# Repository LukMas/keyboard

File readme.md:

# icekeys

A short description of the keyboard/project

Keyboard Maintainer: [You](https://github.com/LukMas)  
Hardware Supported: The PCBs, controllers supported  
Hardware Availability: links to where you can find this hardware

Make example for this keyboard (after setting up your build environment):

    make snowflake:default

Note: check here (https://www.pjrc.com/teensy/td_libs_PS2Keyboard.html) if PS/2 mouse works with other pins. 

See [build environment setup](https://docs.qmk.fm/build_environment_setup.html) then the [make instructions](https://docs.qmk.fm/make_instructions.html) for more information.

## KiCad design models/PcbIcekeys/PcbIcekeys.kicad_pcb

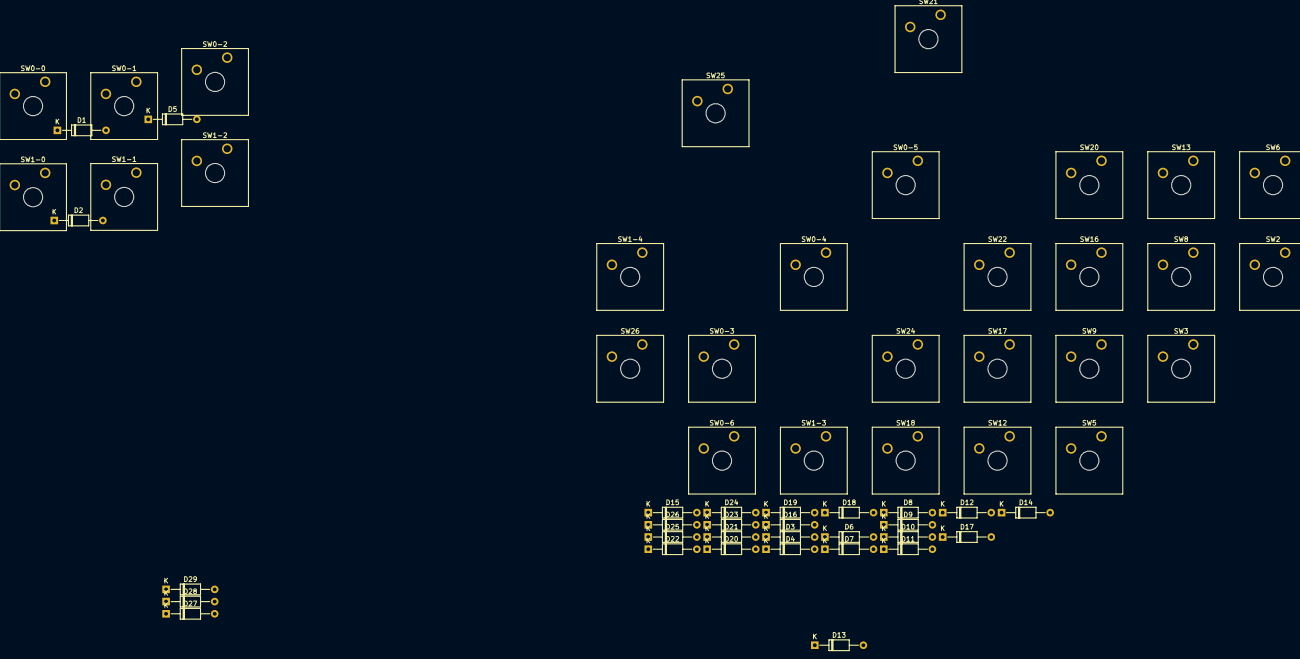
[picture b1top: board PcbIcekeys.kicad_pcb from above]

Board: 2 copper layers, 58 parts (0 on the bottom side), 36 nets, no tracks yet.

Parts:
D1, D2, D3, D4, D5, D6, D7, D8, D9, D10, D11, D12, D13, D14, D15, D16, D17, D18, D19, D20, D21, D22, D23, D24, D25, D26, D27, D28, D29: DIODE; D_DO-35_SOD27_P10.16mm_Horizontal
SW0-0, SW0-1, SW0-2, SW0-3, SW0-4, SW0-5, SW0-6, SW1-0, SW1-1, SW1-2, SW1-3, SW1-4, SW2, SW3, SW5, SW6, SW8, SW9, SW12, SW13, SW16, SW17, SW18, SW20, SW21, SW22, SW24, SW25, SW26: SW_Push; SW_Cherry_MX1A_1.00u_Plate

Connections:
unnamed: D1.1, SW0-0.2
unnamed: D1.2, D5.1, SW0-1.2
unnamed: D2.1, SW1-0.2
unnamed: D2.2, D6.1, SW1-1.2
unnamed: D3.1, SW2.2
unnamed: D3.2, D7.1, SW5.2
unnamed: D4.1, SW3.2
unnamed: D4.2, D8.1, SW6.2
unnamed: D5.2, D9.1, SW0-2.2
unnamed: D6.2, D10.1, SW1-2.2
unnamed: D10.2, D14.1, SW1-3.2
unnamed: D7.2, D11.1, SW8.2
unnamed: D11.2, D15.1, SW12.2
unnamed: D8.2, D12.1, SW9.2
unnamed: D12.2, D16.1, SW13.2
unnamed: D9.2, D13.1, SW0-3.2
unnamed: D13.2, D17.1, SW0-4.2
unnamed: D14.2, D18.1, SW1-4.2
unnamed: D15.2, D19.1, SW16.2
unnamed: D16.2, D20.1, SW17.2
unnamed: D17.2, D22.1, SW0-5.2
unnamed: D18.2, D23.1, SW20.2
unnamed: D19.2, D24.1, SW21.2
unnamed: D20.2, D21.1, SW18.2
unnamed: D21.2, D25.1, SW22.2
unnamed: D22.2, D26.1, SW0-6.2
unnamed: D23.2, D27.1, SW24.2
unnamed: D24.2, D28.1, SW25.2
unnamed: D25.2, D29.1, SW26.2
unnamed: SW0-0.1, SW1-0.1, SW2.1, SW3.1
unnamed: SW0-1.1, SW1-1.1, SW5.1, SW6.1
unnamed: SW0-2.1, SW1-2.1, SW8.1, SW9.1
unnamed: SW0-3.1, SW1-3.1, SW12.1, SW13.1
unnamed: SW0-4.1, SW1-4.1, SW16.1, SW17.1, SW18.1
unnamed: SW0-5.1, SW20.1, SW21.1, SW22.1
unnamed: SW0-6.1, SW24.1, SW25.1, SW26.1

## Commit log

2018-08-09 Initial version of IceKeys keyboard
    Initial version of the keyboad IceKeys.
    In this firt revision only some keys are used. Actually the layout is
    used for understanding how the keys, the macros and the functionalities
    of QMK work.
2018-08-09 Removed files and configured .gitignore
    Temp files have been removed from repository.
    Gitignore has been cofigured to ignore this files in the future.
2018-08-09 Added tne Navi Layer
    The layout now supports a new layer, the Navi Layer, where the mouse
    keys are added.
    It's a LT type, held will activate the layer, tap will activate the tab.
2018-08-10 Mouse Navigation layer - Navi layer
    Added new layer to the keyboard: Navi layer.
    Selectable with holding the tab, it offers the basic mouse movements and
    keys.
2018-09-17 PS/2 mouse and DXF
    Added a DXF with the first draft of the mechanical structure of the
    keyboard.
    Activated the PS/2 mouse support (still not working).
2018-09-17 Model layouts
2018-09-20 Added multiple layers to model
    Added multiple layers to the model of the keyboard. Now Also the top
    layer, with round borders, is defined.
2018-09-21 Leds holes and description
    Added the holes for the leds and a description of the structure of the
    keyboard.
    Still to decide:
    - dimension (heigth)
    - use of single leds or strips
2018-09-21 Added link with info about teensy
2018-09-22 Activate PS/2 Mouse using USART
    The firmware now supports the use of a PS/2 Mouse using the USART mode.
    A small circuitry is needed between the module and the controller.
2018-09-22 Led on/off on TapDance
    The led is controller also during the tap dance functionality.
    Whenever the User taps the LShift, the led turns on for all the time
    that the tap dance is active. when is deactivated, also the led is
    turned off.
2018-10-01 Multiple Layers, 6 holes to fix the sides
2018-10-02 Wide Border with 6 fix points
2018-10-04 New model
2018-10-04 Final cutouts
    Final cutouts for the 2 sides of the keyboard.
    The other layers are still in development, but the metal plate, where
    the keys will be locked, is completed.
    Sent to the laser company for the cut.
2018-12-06 Model and Keyboard updates
    New model of hardware.
    No PCB is planned. Wood case will be updated with Plexyglass later on.
    Starting to define the final wiring and the keys of the keyboard.
2018-12-10 13 - Layout for all the Keys of the Keyboard
    Definition of the layout for all the keys that are in the keyboard.
    First drafts of the layers that will be present in the keyboard.
2019-02-26 14 - Layout for Keybòard
    Layout for keyboard.
2019-02-28 With media keys
2019-02-28 Corrected error, added sleep media key
2019-02-28 Small change in layout
2019-02-28 Cleaned layers maps
2019-03-06 Changes in layout
2019-03-07 Palmrest dxf
2019-03-07 Updated and tested the .gitignore file
2019-03-08 Update of the layout
2019-03-08 Corrected position of F keys
2019-03-12 Extra layout with multiple mod keys
2019-03-13 better handling of ESC to disable layouts
2019-03-13 Better using of LEDs
2019-03-13 Better improve of LEDs
2019-03-15 Removed one shot keys and added special behavior to modifiers
2019-03-16 Refactoring of the layout macro, moved keys around
2019-03-18 Improved the Space Cadet keys
2019-03-18 LEDs power increased
2019-03-20 Changed the way the ({[ are handled
2019-03-20 Tap dance with mod keys to simulate space cadet
2019-03-21 Tap for mods/par.
2019-04-23 Tap dance to select keys and layer
2019-08-08 Better definitions of parentesis
2020-03-25 Added extra layer
2020-07-07 Updated keys layout
2020-07-16 Removed navigation crossings
2020-07-16 Moved NAVI layer switch
2020-07-17 Moved navi layer selection key
2020-07-20 Removed keys from keyboard
2020-07-20 Removed ins/app from NAVI
2020-07-22 Changed one-shot timeout
2020-07-22 Moved NAVI switch
2020-07-23 Removed key to NAVI, added 2 extra keys
2020-07-24 Changed the parenthesis
2020-07-27 Moved NAVI switch key
2020-09-04 Removed unused keys
2020-09-16 Lock instead of suspend
2020-11-10 Test split
